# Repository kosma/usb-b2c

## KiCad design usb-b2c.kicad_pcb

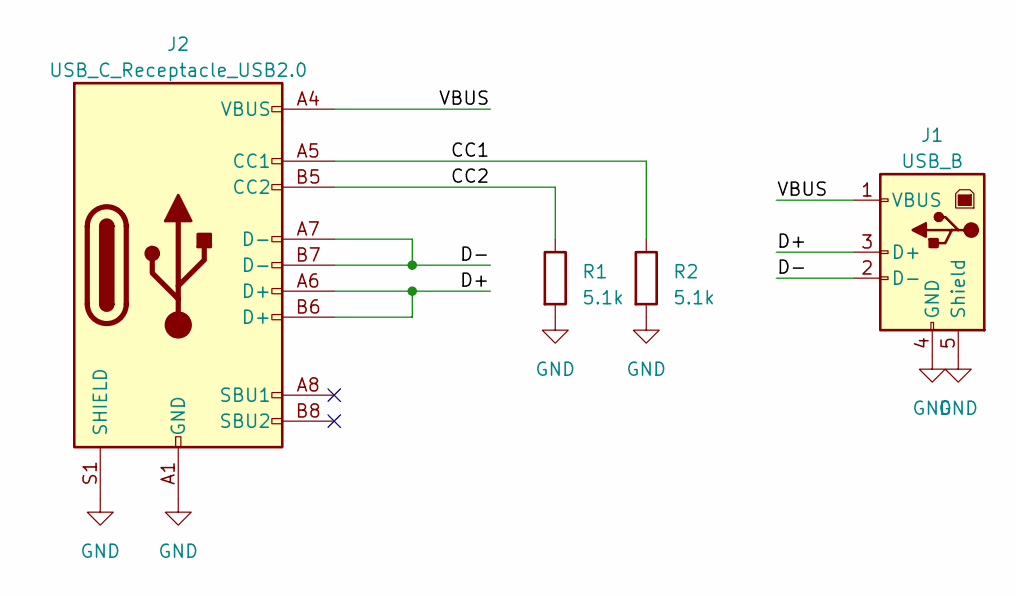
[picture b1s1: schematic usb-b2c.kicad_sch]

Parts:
J1: USB_B; USB_B_Lumberg_2411_02_Horizontal
J2: USB_C_Receptacle_USB2.0; USB_C_Receptacle_GCT_USB4105-xx-A_16P_TopMnt_Horizontal
R1, R2: 5.1k; R_0603_1608Metric

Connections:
/CC1: J2.A5 (CC1), R2.1
/CC2: J2.B5 (CC2), R1.1
/D+: J1.3 (D+), J2.A6 (D+), J2.B6 (D+)
/D-: J1.2 (D-), J2.A7 (D-), J2.B7 (D-)
/VBUS: J1.1 (VBUS), J2.A4 (VBUS), J2.A9 (VBUS), J2.B4 (VBUS), J2.B9 (VBUS)
GND: J1.4 (GND), J1.5 (Shield), J2.A1 (GND), J2.A12 (GND), J2.B1 (GND), J2.B12 (GND), J2.S1 (SHIELD), R1.2, R2.2

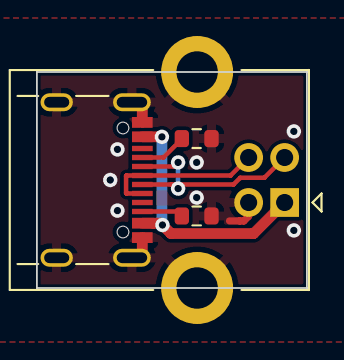
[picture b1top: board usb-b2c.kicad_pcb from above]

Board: 2 copper layers, 15.0 x 12.0 mm, 4 parts (0 on the bottom side), 6 nets.

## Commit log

2023-05-27 first version
2024-06-19 prepare for manufacturing
2024-06-19 add production file
